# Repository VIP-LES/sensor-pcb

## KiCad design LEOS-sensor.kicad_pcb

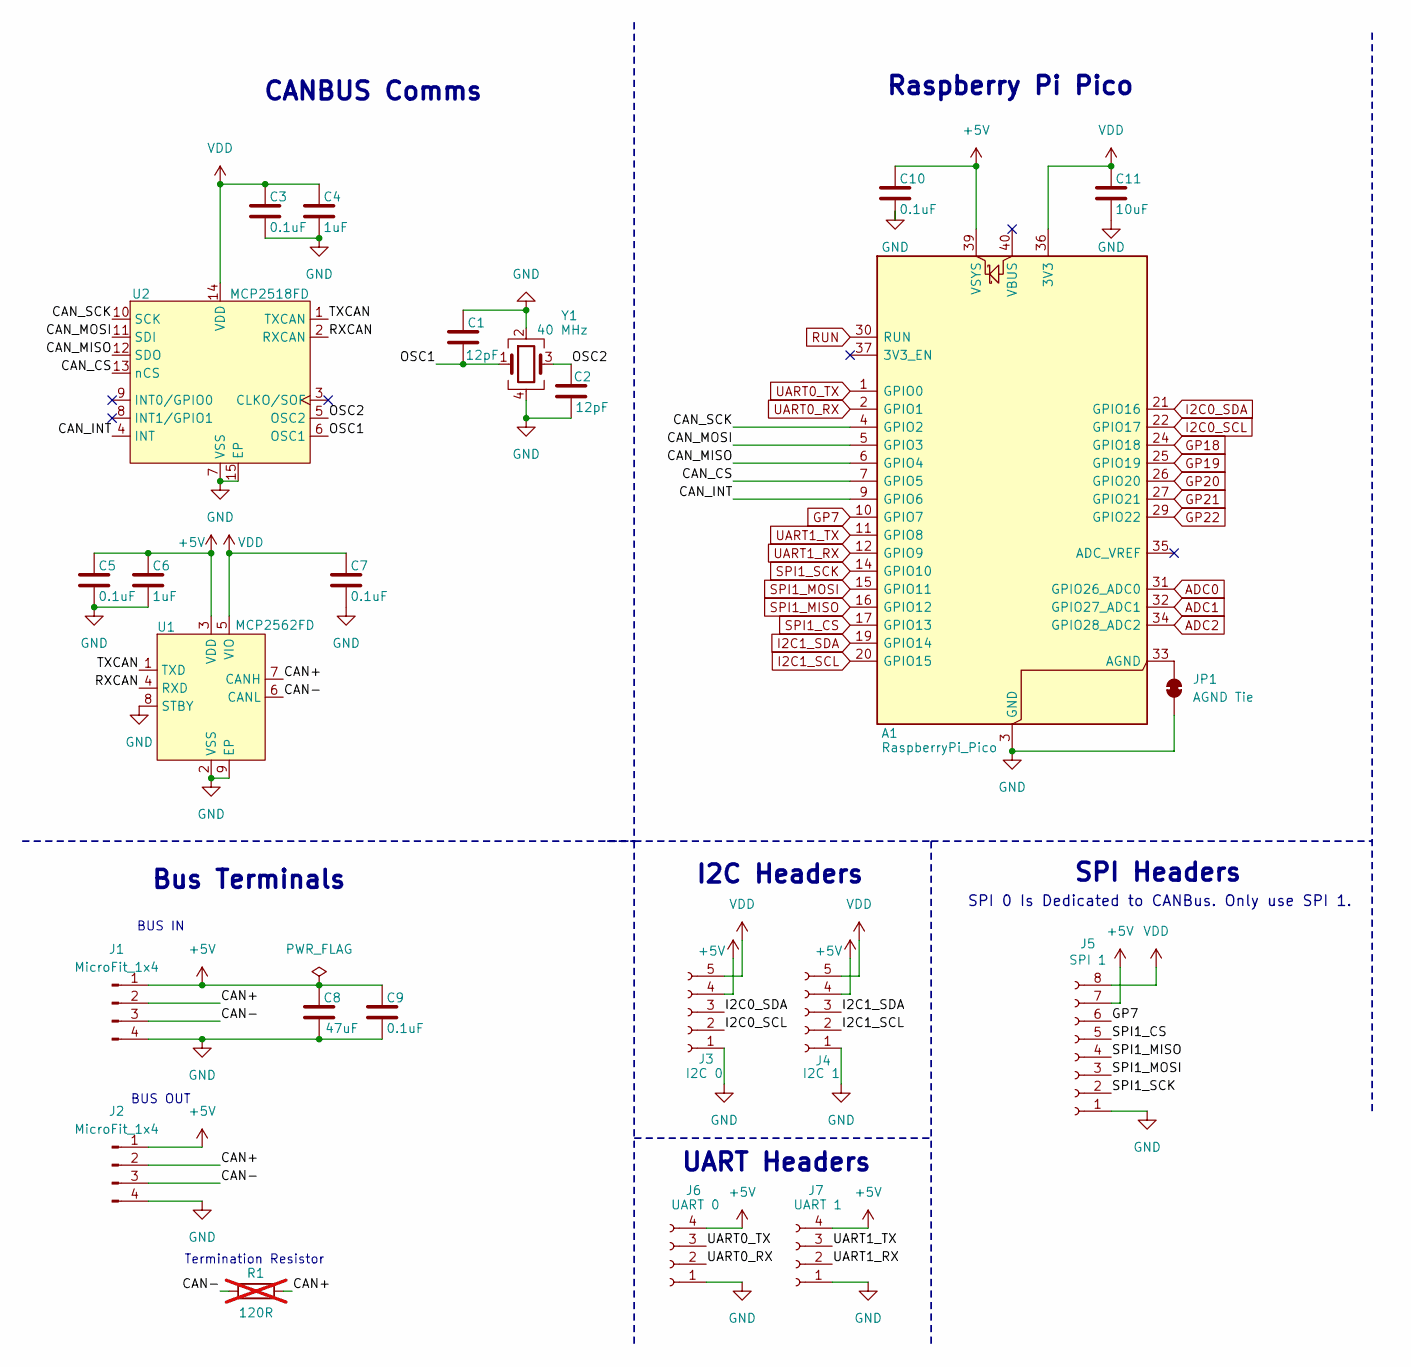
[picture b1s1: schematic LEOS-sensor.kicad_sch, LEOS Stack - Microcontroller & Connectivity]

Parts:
A1: RaspberryPi_Pico; RaspberryPi_Pico_Common_THT
C1, C2: 12pF; C_0603_1608Metric
C3, C5, C7, C9, C10: 0.1uF; C_0603_1608Metric
C4, C6: 1uF; C_0603_1608Metric
C8: 47uF; C_0603_1608Metric
C11: 10uF; C_0603_1608Metric
J1, J2: MicroFit_1x4; Molex_Micro-Fit_3.0_43650-0410_1x04-1MP_P3.00mm_Horizontal_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
J3: I2C 0; PinSocket_1x05_P2.54mm_Horizontal
J4: I2C 1; PinSocket_1x05_P2.54mm_Horizontal
J5: SPI 1; PinSocket_1x08_P2.54mm_Horizontal
J6: UART 0; PinSocket_1x04_P2.54mm_Horizontal
J7: UART 1; PinSocket_1x04_P2.54mm_Horizontal
JP1: AGND Tie; SolderJumper-2_P1.3mm_Bridged_RoundedPad1.0x1.5mm
R1: 120R; R_Axial_DIN0207_L6.3mm_D2.5mm_P7.62mm_Horizontal; not fitted
U1: MCP2562FD; SOIC-8_3.9x4.9mm_P1.27mm
U2: MCP2518FD; SOIC-14_3.9x8.7mm_P1.27mm
Y1: 40 MHz; Crystal_SMD_3225-4Pin_3.2x2.5mm_HandSoldering

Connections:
+5V: A1.39 (VSYS), C5.1, C6.1, C8.1, C9.1, C10.1, J1.1, J2.1, J3.4, J4.4, J5.7, J6.4, J7.4, U1.3 (VDD)
/CAN+: J1.2, J2.2, R1.2, U1.7 (CANH)
/CAN-: J1.3, J2.3, R1.1, U1.6 (CANL)
/CAN_CS: A1.7 (GPIO5), U2.13 (nCS)
/CAN_INT: A1.9 (GPIO6), U2.4 (INT)
/CAN_MISO: A1.6 (GPIO4), U2.12 (SDO)
/CAN_MOSI: A1.5 (GPIO3), U2.11 (SDI)
/CAN_SCK: A1.4 (GPIO2), U2.10 (SCK)
/OSC1: C1.1, U2.6 (OSC1), Y1.1
/OSC2: C2.2, U2.5 (OSC2), Y1.3
/RXCAN: U1.4 (RXD), U2.2 (RXCAN)
/TXCAN: U1.1 (TXD), U2.1 (TXCAN)
ADC0: A1.31 (GPIO26_ADC0)
ADC1: A1.32 (GPIO27_ADC1)
ADC2: A1.34 (GPIO28_ADC2)
GND: A1.3 (GND), A1.8 (GND), A1.13 (GND), A1.18 (GND), A1.23 (GND), A1.28 (GND), A1.38 (GND), C1.2, C2.1, C3.2, C4.2, C5.2, C6.2, C7.2, C8.2, C9.2, C10.2, C11.2, J1.4, J2.4, J3.1, J4.1, J5.1, J6.1, J7.1, JP1.1 (A), U1.2 (VSS), U1.8 (STBY), U1.9 (EP), U2.7 (VSS), U2.15 (EP), Y1.2, Y1.4
GP7: A1.10 (GPIO7), J5.6
GP18: A1.24 (GPIO18)
GP19: A1.25 (GPIO19)
GP20: A1.26 (GPIO20)
GP21: A1.27 (GPIO21)
GP22: A1.29 (GPIO22)
I2C0_SCL: A1.22 (GPIO17), J3.2
I2C0_SDA: A1.21 (GPIO16), J3.3
I2C1_SCL: A1.20 (GPIO15), J4.2
I2C1_SDA: A1.19 (GPIO14), J4.3
unnamed: A1.33 (AGND), JP1.2 (B)
RUN: A1.30 (RUN)
SPI1_CS: A1.17 (GPIO13), J5.5
SPI1_MISO: A1.16 (GPIO12), J5.4
SPI1_MOSI: A1.15 (GPIO11), J5.3
SPI1_SCK: A1.14 (GPIO10), J5.2
UART0_RX: A1.2 (GPIO1), J6.2
UART0_TX: A1.1 (GPIO0), J6.3
UART1_RX: A1.12 (GPIO9), J7.2
UART1_TX: A1.11 (GPIO8), J7.3
VDD: A1.36 (3V3), C3.1, C4.1, C7.1, C11.1, J3.5, J4.5, J5.8, U1.5 (VIO), U2.14 (VDD)

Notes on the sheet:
CANBUS Comms
SPI 0 Is Dedicated to CANBus. Only use SPI 1.
Raspberry Pi Pico
I2C Headers
SPI Headers
BUS IN
UART Headers
Termination Resistor
BUS OUT
Bus Terminals

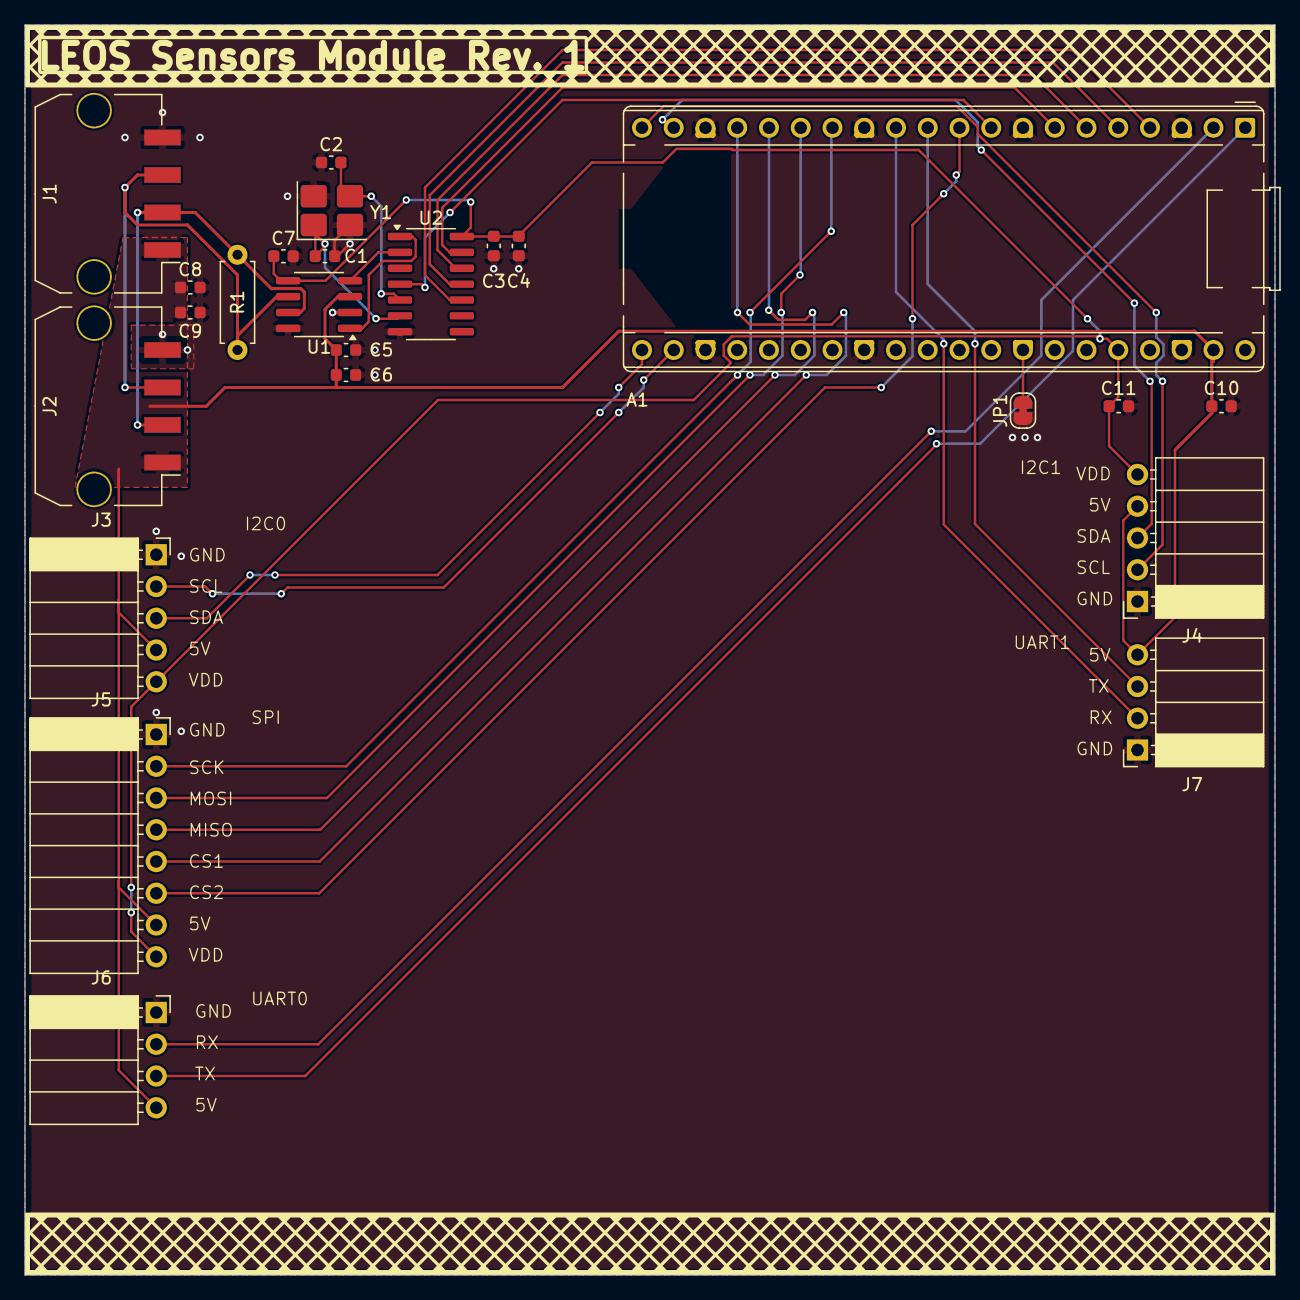
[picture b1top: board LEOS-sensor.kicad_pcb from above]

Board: 2 copper layers, 100.0 x 100.0 mm, 24 parts (0 on the bottom side), 28 nets.

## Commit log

2025-09-27 Routed and schematiced sensor board
2025-09-30 Converted schematic to Socket schematics and routed all headers
2025-09-30 added labels to pin connectors on pcb
